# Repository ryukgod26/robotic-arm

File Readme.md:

# Robotic Arm
This is a Simple Robotic arm created by me. It just uses 3 Servo Motors 1 one for gripper and 2 for the arm. This is just a Basic arm for now because I could not make good jaws right now and will improvise the robotic after on.

## Why
I created this project because it is cool and i wanted to make it one (Because I saw it in Iron man movies). I Built this Project to get to know about how structure and detailing in Fusion 360 can effect the full Project. I want to integrate in it later (just liek Iron man again) and amke it even cooler.

## Zine

## Required Hardware

Servo Motors X 3
Esp32 X 1
Battery X 1
Battery Charging Module X 1
Booster Module X 1
Bunch of Cables

## BOM (Bill of Materials)

| Name | Quantity | Total Cost (USD) | Link | Distributor |
|------|----------|------------------|------|-------------|
|ESP32| 1 | $4.00 | [Quartz](https://quartzcomponents.com/collections/all/products/esp32-30-pin-development-board-with-wi-fi-and-bluetooth) | Quartz Components |
| Servo Motor | 3 | $7.5 | [Quartz](https://quartzcomponents.com/products/mg995-metal-gear-servo-motor-180-degree-rotation) | Quartz Components |
| TP4056 | 1 | $0.2 | [Robu](https://robu.in/product/tp4056-1a-li-ion-battery-charging-board-micro-usb-with-current-protection-type-c-connector/) | Robu |
| Booster Module | 1 | $0.3 | [robu](https://robu.in/product/mt3608-2a-max-dc-dc-step-up-power-module-booster-power-module/) | Robu |
| Total | 6 | $12.00 |  |  |

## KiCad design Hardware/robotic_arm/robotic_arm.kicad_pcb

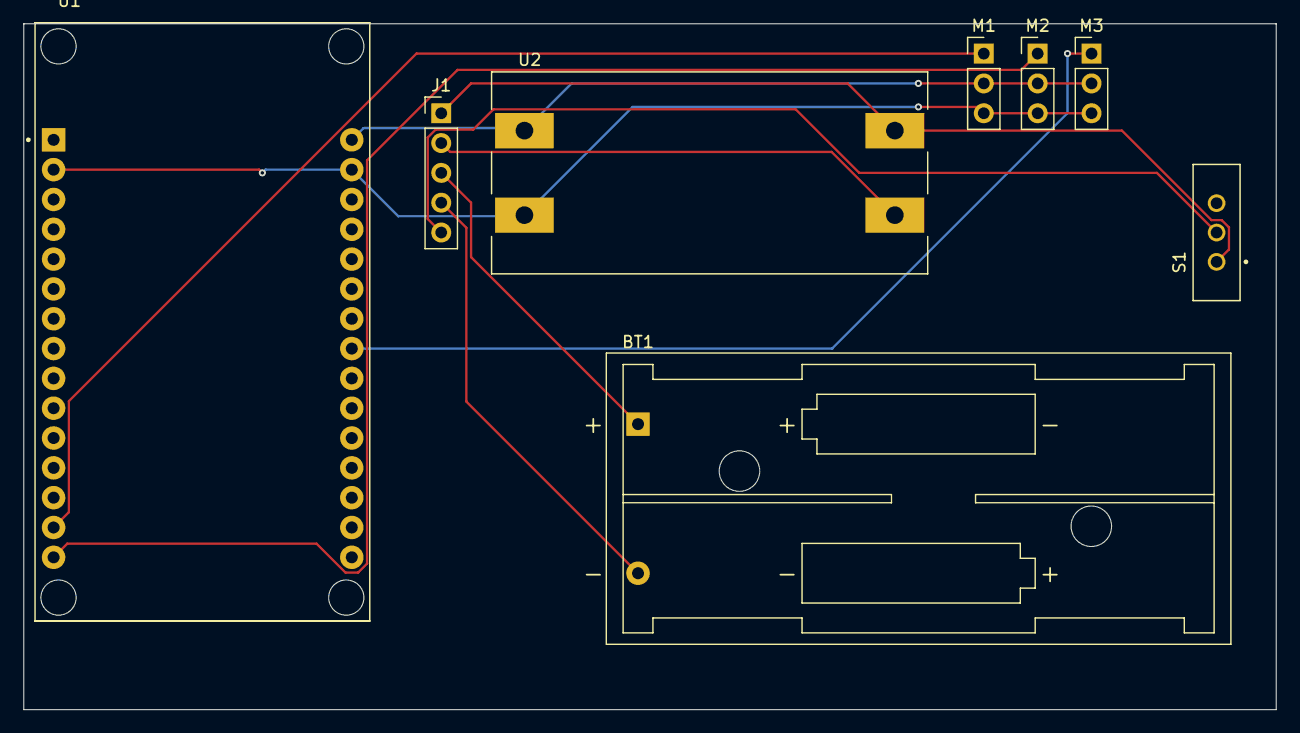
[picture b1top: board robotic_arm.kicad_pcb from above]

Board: 2 copper layers, 106.7 x 58.4 mm, 8 parts (0 on the bottom side), 10 nets.

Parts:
BT1: Battery; BatteryHolder_Keystone_2468_2xAAA
J1: Conn_01x06; PinHeader_1x05_P2.54mm_Vertical
M1, M2, M3: Motor_Servo; PinHeader_1x03_P2.54mm_Vertical
S1: EG1218; SW_EG1218
U1: ESP32-DEVKIT-V1; MODULE_ESP32_DEVKIT_V1
U2: MT3608_DC-DC_STEP_UP_CONVERTER_2A_BOOSTER_MODULE; MODULE_MT3608_DC-DC_STEP_UP_CONVERTER_2A_BOOSTER_MODULE

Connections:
/B+: BT1.1 (+), J1.3
/B-: BT1.2 (-), J1.4
/IN+: J1.5, S1.2
/OUT+: J1.1, S1.1, U2.VIN_P (VIN+)
/OUT-: J1.2, U2.VIN_N (VIN-)
GND: M1.3 (-), M2.3 (-), M3.3 (-), U1.2 (GND), U1.29 (GND), U2.VOUT_N (VOUT-)
unnamed: M1.2 (+), M2.2 (+), M3.2 (+), U1.30 (VIN), U2.VOUT_P (VOUT+)
unnamed: M1.1 (PWM), U1.14 (D22)
unnamed: M2.1 (PWM), U1.15 (D23)
unnamed: M3.1 (PWM), U1.23 (D25)

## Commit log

2026-06-09 Added 3D Models for esp32 and craeted 3D Model of BAse of robotic Arm
2026-06-09 Added more supports and dsetails in the Base
2026-06-09 Added 3D Model of Jaw
2026-06-10 Added more detailing in the Jaw
2026-06-10 Added 3D Model of the Jaw2
2026-06-21 Add initial project files for robotic arm including schematics, images, and documentation
    - Created sym-lib-table for component libraries used in the project
    - Added QR code images for project identification
    - Included images of the robotic arm for visual reference
    - Added a README.md file detailing project purpose, required hardware, and BOM
    - Documented project progress in robotic-arm-journal.md with multiple entries
    - Added zine assets including images and PDF for project presentation
2026-06-21 Add initial implementation of robotic arm control with web interface
2026-06-21 Fix formatting in BOM.csv to use commas as delimiters
2026-06-21 Update zine images: replace zine.jpg and zine.png with new versions
2026-06-23 Add new 3D model files for robotic arm components and related assets
2026-06-26 Update BOM in Readme.md and BOM.csv to include total cost and ensure consistency
